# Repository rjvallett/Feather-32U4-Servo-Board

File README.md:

# Feather-32U4-Servo-Board
An EAGLE CAD PCB designed to connect with the Adafruit Feather 32U4 Bluetooth LE microcontroller.

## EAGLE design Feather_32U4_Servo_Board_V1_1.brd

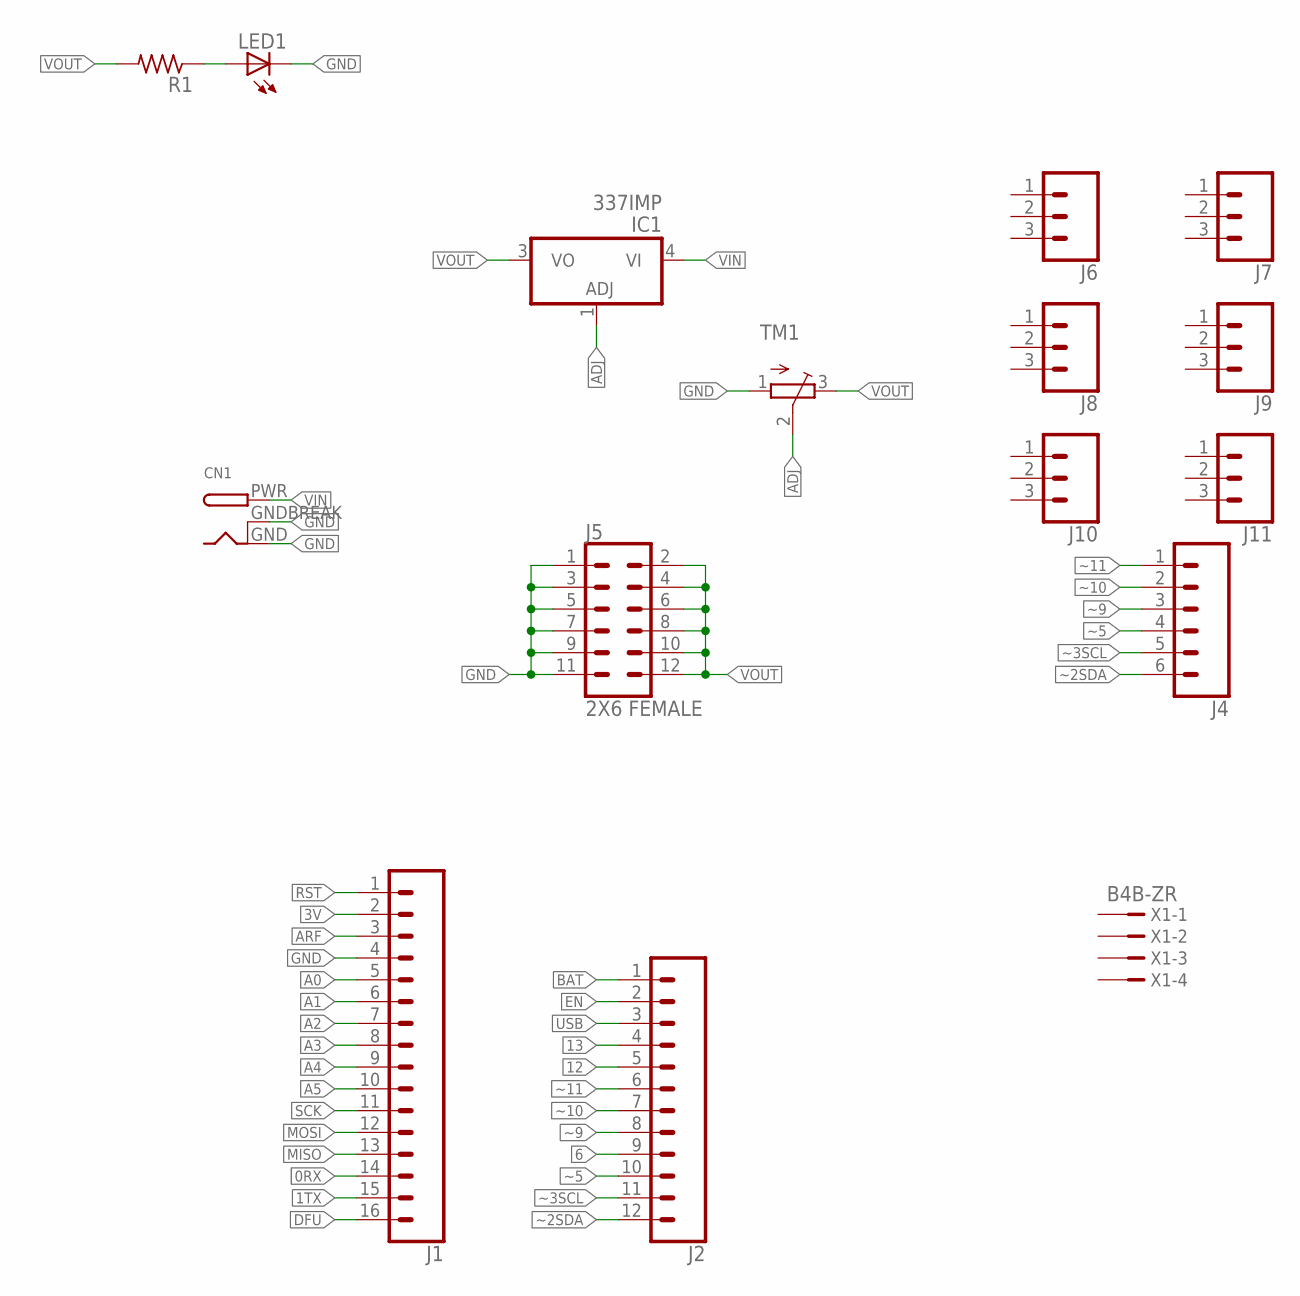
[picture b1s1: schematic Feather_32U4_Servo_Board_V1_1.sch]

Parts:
CN1: DCBARRELPTH; DCJACK_2MM_PTH
IC1: 337IMP; SOT223
J1: CONN_16; 1X16
J2: CONN_12; 1X12
J4: CONN_06SILK_FEMALE_PTH; 1X06
J5: 2X6 FEMALE; 2X6
J6, J7, J8, J9, J10, J11: CONN_03POLAR; MOLEX-1X3
LED1: LEDCHIPLED_0805; CHIPLED_0805
R1: R-US_M0805; M0805
TM1: TRIMPOTTC33X; TC33X
X1: B4B-ZR

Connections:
0RX: J1.14
1TX: J1.15
3V: J1.2
6: J2.9
12: J2.5
13: J2.4
A0: J1.5
A1: J1.6
A2: J1.7
A3: J1.8
A4: J1.9
A5: J1.10
ADJ: IC1.1 (ADJ), TM1.2 (S)
ARF: J1.3
BAT: J2.1
DFU: J1.16
EN: J2.2
GND: CN1.GND, CN1.GNDBREAK, J1.4, J5.1, J5.3, J5.5, J5.7, J5.9, J5.11, LED1.C, TM1.1 (A)
MISO: J1.13
MOSI: J1.12
unnamed: LED1.A, R1.1
RST: J1.1
SCK: J1.11
USB: J2.3
VIN: CN1.PWR, IC1.4 (VI)
VOUT: IC1.3 (VO), J5.2, J5.4, J5.6, J5.8, J5.10, J5.12, R1.2, TM1.3 (E)
~2SDA: J2.12, J4.6
~3SCL: J2.11, J4.5
~5: J2.10, J4.4
~9: J2.8, J4.3
~10: J2.7, J4.2
~11: J2.6, J4.1

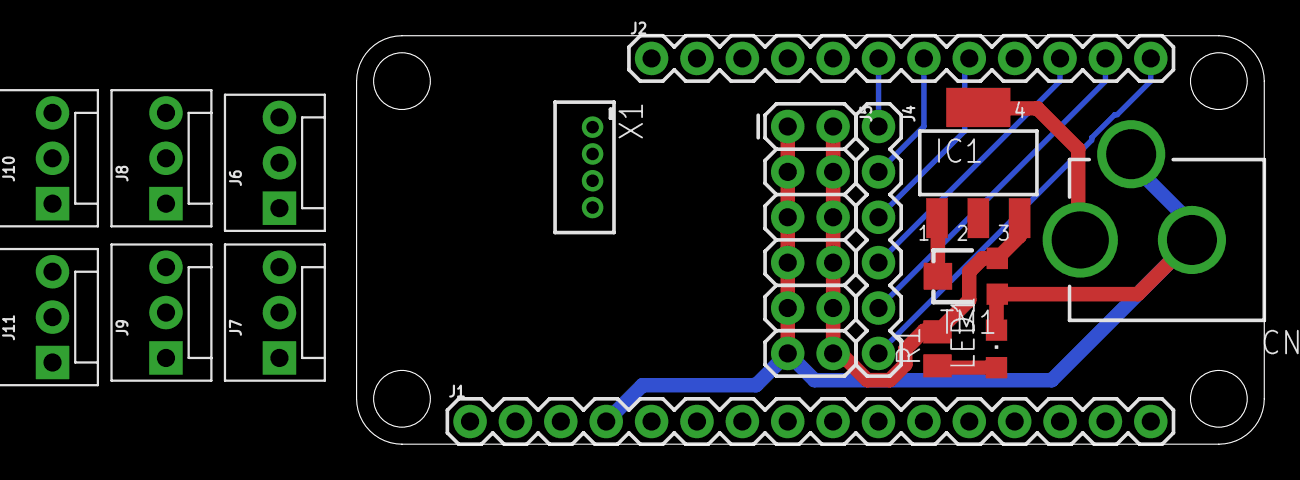
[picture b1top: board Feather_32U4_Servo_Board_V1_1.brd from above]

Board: 2 copper layers, 50.8 x 22.9 mm, 16 parts (0 on the bottom side), 11 nets.

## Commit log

2019-06-25 Initial upload.

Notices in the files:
parts and their libraries:
SparkFun-Connectors: Licensing: Creative Commons ShareAlike 4.0 International - https://creativecommons.org/licenses/by-sa/4.0
